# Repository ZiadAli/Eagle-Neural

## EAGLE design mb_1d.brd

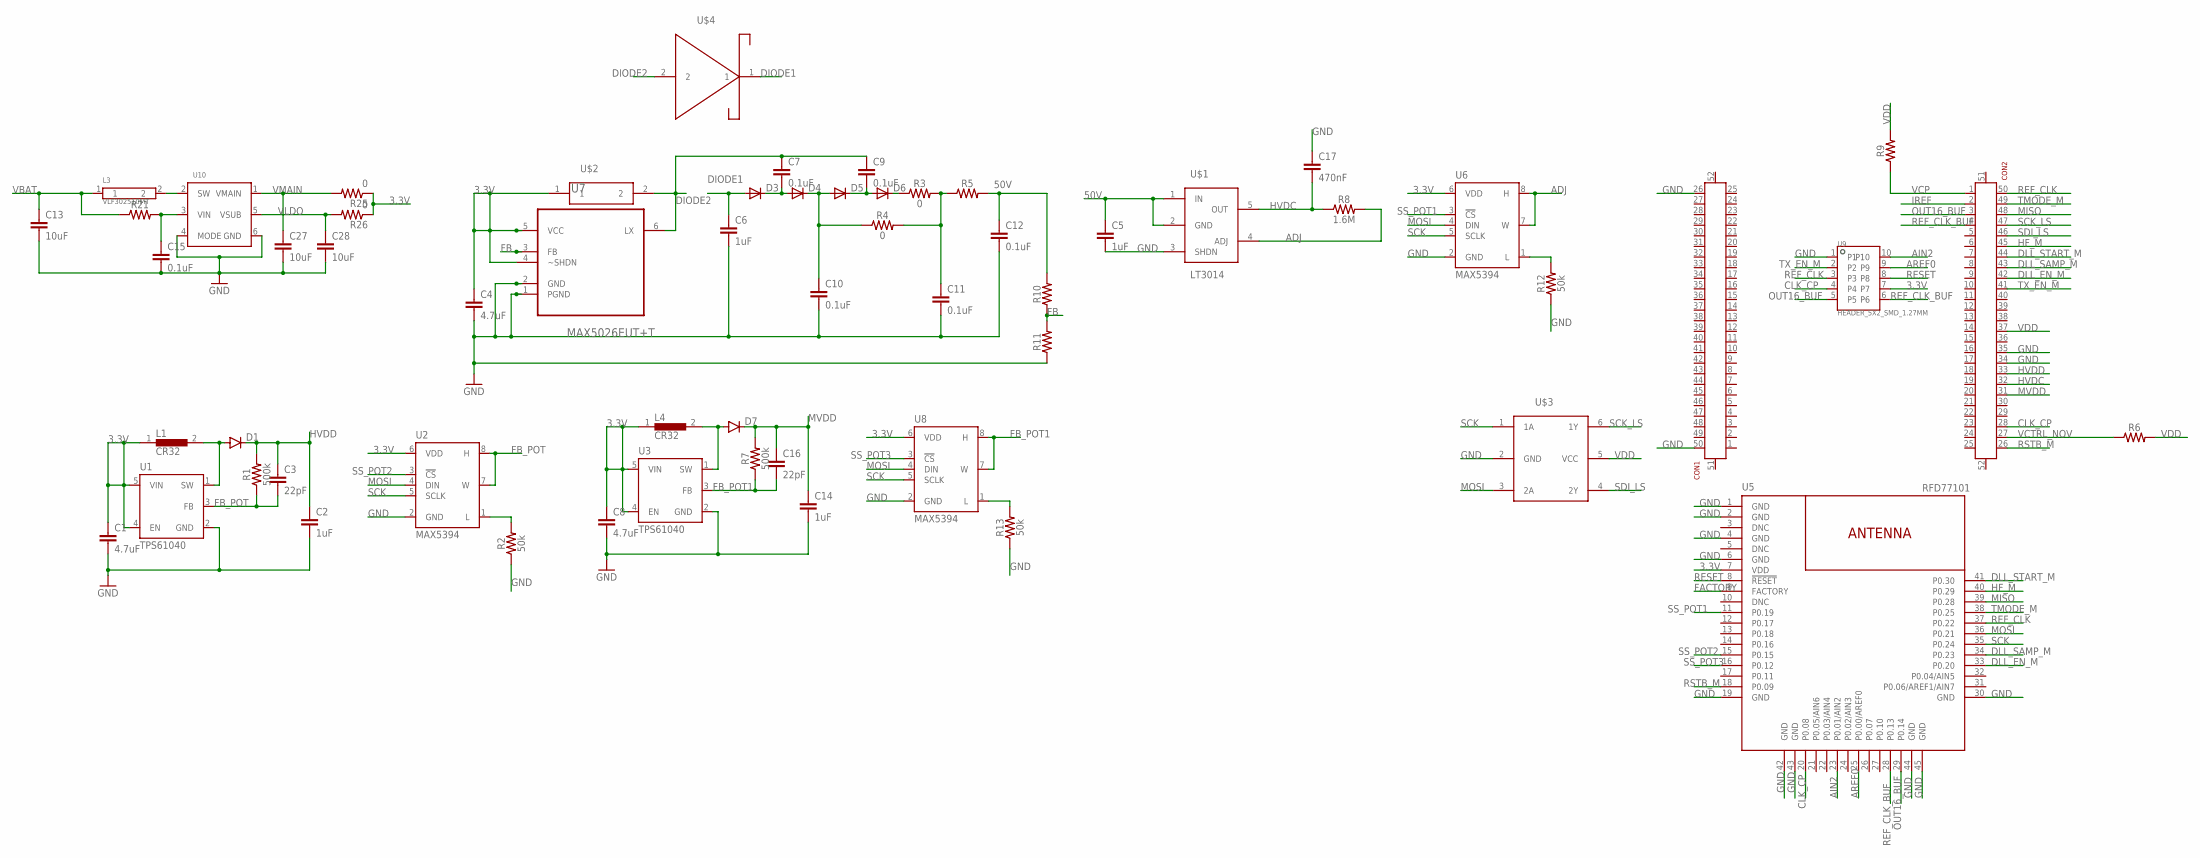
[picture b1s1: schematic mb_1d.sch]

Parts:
C1, C4, C8: 4.7uF; 0805-CAP
C2, C5, C6, C14: 1uF; 1206-CAP
C3, C16: 22pF; 0603-CAP
C7, C9, C10, C11, C12: 0.1uF; 0402
C13, C27, C28: 10uF; 0603-CAP
C15: 0.1uF; 0603-CAP
C17: 470nF; 0402
CON1, CON2: 1013279X_AMPHENOL_2X25; 10132798-052100LF
D1, D7: DIODESOD123; SOD-123
D3, D4, D5, D6: DIODE-SOD323-R; SOD323-R
L1, L4: CR32
L3: VLF302510MT; VLF252010MT
R1, R7: 500k; 0402
R2, R12, R13: 50k; 0402
R3, R4: 0; 0402
R5, R6, R9, R10, R11: 0402
R8: 1.6M; 0402
R21: 0603
R25, R26: 0; 0402-RES
U1, U3: TPS61040; SOT23-5
U2, U6, U8: MAX5394; 8-TDFN-EP
U5: RFD77101
U7: MAX5026EUT+T; SOT95P280X145-6N
U9: HEADER_5X2_SMD_1.27MM
U10: TPS610981; WSON-6
U$1: LT3014
U$2: LQH3NPN470MJRL
U$3: SN74AUP2G34DCKR
U$4: DB2J40700L

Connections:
3.3V: C1.1, C4.1, C8.1, L1.1, L4.1, R25.1, R26.1, U1.4 (EN), U1.5 (VIN), U2.6 (VDD), U3.4 (EN), U3.5 (VIN), U5.7 (VDD), U6.6 (VDD), U7.4 (~SHDN), U7.5 (VCC), U8.6 (VDD), U9.7, U$2.1
50V: C5.1, C12.1, R5.2, R10.2, U$1.1 (IN), U$1.2 (GND)
ADJ: R8.2, U6.7 (W), U6.8 (H), U$1.4 (ADJ)
AIN2: U5.23 (P0.01/AIN2), U9.10
AREF0: U5.25 (P0.00/AREF0), U9.9
CLK_CP: CON2.28, U5.20 (P0.08), U9.4
DIODE1: C6.1, D3.A, U$4.1
DIODE2: C7.1, C9.1, U7.6 (LX), U$2.2, U$4.2
DLL_EN_M: CON2.42, U5.33 (P0.20)
DLL_SAMP_M: CON2.43, U5.34 (P0.23)
DLL_START_M: CON2.44, U5.41 (P0.30)
FACTORY: U5.9 (FACTORY)
FB: R10.1, R11.2, U7.3 (FB)
FB_POT: C3.2, R1.1, U1.3 (FB), U2.7 (W), U2.8 (H)
FB_POT1: C16.2, R7.1, U3.3 (FB), U8.7 (W), U8.8 (H)
GND: C1.2, C2.2, C4.2, C5.2, C6.2, C8.2, C10.2, C11.2, C12.2, C13.2, C14.2, C15.2, C17.1, C27.2, C28.2, CON1.26, CON1.50, CON2.34, CON2.35, R2.1, R11.1, R12.1, R13.1, U1.2 (GND), U2.2 (GND), U3.2 (GND), U5.1 (GND), U5.2 (GND), U5.4 (GND), U5.6 (GND), U5.19 (GND), U5.30 (GND), U5.42 (GND), U5.43 (GND), U5.44 (GND), U5.45 (GND), U6.2 (GND), U7.1 (PGND), U7.2 (GND), U8.2 (GND), U9.1, U10.4 (MODE), U10.6 (GND), U$1.3 (SHDN), U$3.2 (GND)
HF_M: CON2.45, U5.40 (P0.29)
HVDC: C17.2, CON2.32, R8.1, U$1.5 (OUT)
HVDD: C2.1, C3.1, CON2.33, D1.C, R1.2
IREF: CON2.2
MISO: CON2.48, U5.39 (P0.28)
MOSI: U2.4 (DIN), U5.36 (P0.21), U6.4 (DIN), U8.4 (DIN), U$3.3 (2A)
MVDD: C14.1, C16.1, CON2.31, D7.C, R7.2
unnamed: D1.A, L1.2, U1.1 (SW)
unnamed: R2.2, U2.1 (L)
unnamed: C7.2, D3.C, D4.A
unnamed: C10.1, D4.C, D5.A, R4.1
unnamed: C9.2, D5.C, D6.A
unnamed: D6.C, R3.1
unnamed: C11.1, R3.2, R4.2, R5.1
unnamed: D7.A, L4.2, U3.1 (SW)
unnamed: R12.2, U6.1 (L)
unnamed: R13.2, U8.1 (L)
unnamed: L3.2, U10.2 (SW)
unnamed: C15.1, R21.2, U10.3 (VIN)
OUT16_BUF: CON2.3, U5.29 (P0.14), U9.5
REF_CLK: CON2.50, U5.37 (P0.22), U9.3
REF_CLK_BUF: CON2.4, U5.28 (P0.13), U9.6
RESET: U5.8 (!RESET!), U9.8
RSTB_M: CON2.26, U5.18 (P0.09)
SCK: U2.5 (SCLK), U5.35 (P0.24), U6.5 (SCLK), U8.5 (SCLK), U$3.1 (1A)
SCK_LS: CON2.47, U$3.6 (1Y)
SDI_LS: CON2.46, U$3.4 (2Y)
SS_POT1: U5.11 (P0.19), U6.3 (!CS)
SS_POT2: U2.3 (!CS), U5.15 (P0.15)
SS_POT3: U5.16 (P0.12), U8.3 (!CS)
TMODE_M: CON2.49, U5.38 (P0.25)
TX_EN_M: CON2.41, U9.2
VBAT: C13.1, L3.1, R21.1
VCP: CON2.1, R9.1
VCTRL_NOV: CON2.27, R6.1
VDD: CON2.37, R6.2, R9.2, U$3.5 (VCC)
VLDO: C28.1, R26.2, U10.5 (VSUB)
VMAIN: C27.1, R25.2, U10.1 (VMAIN)

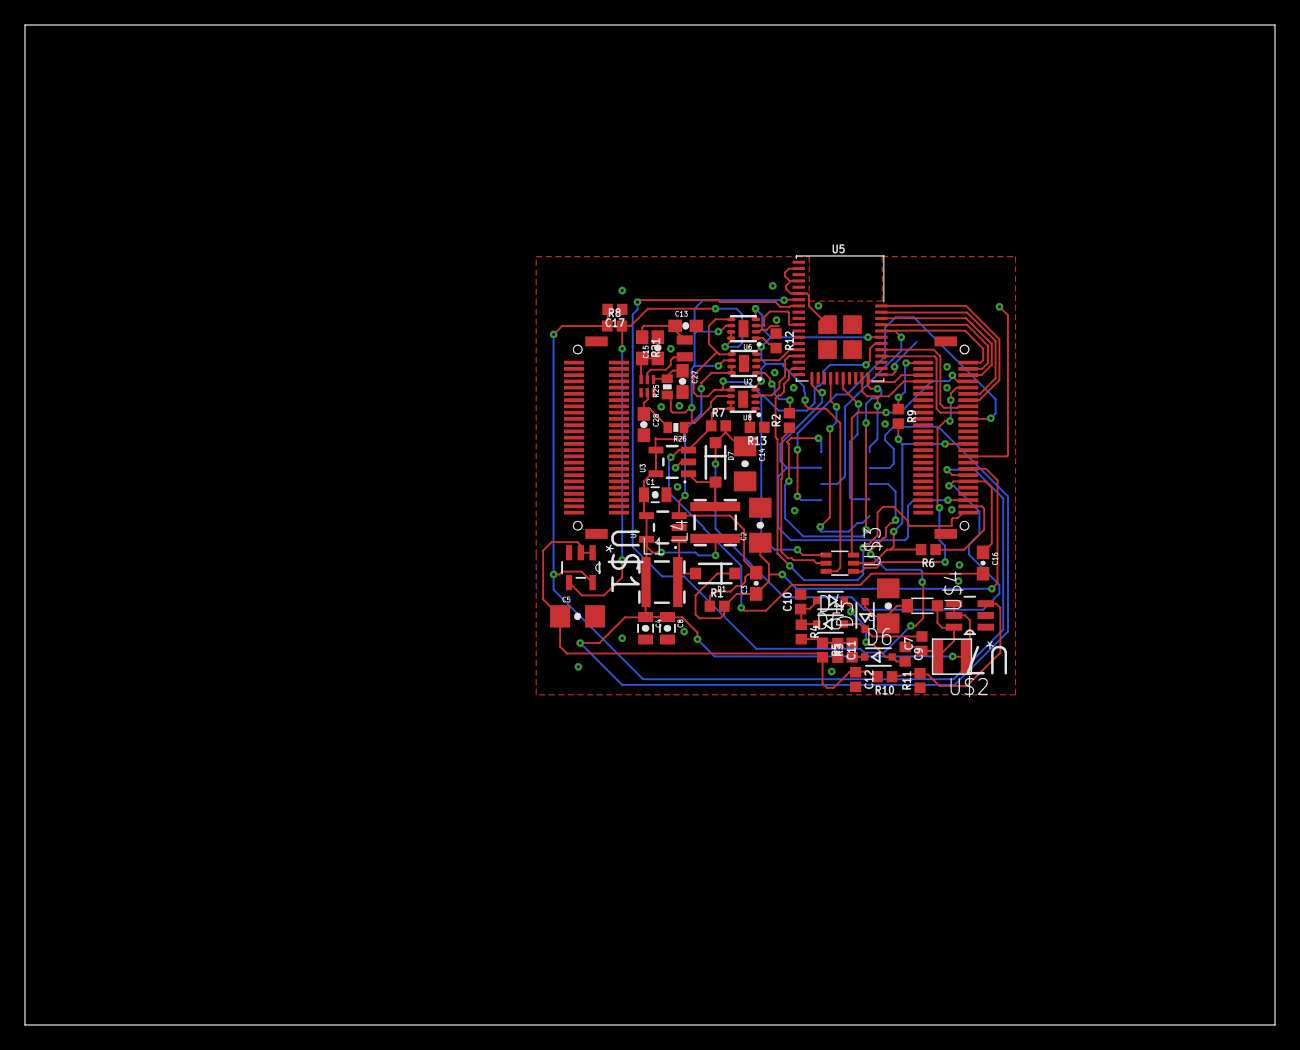
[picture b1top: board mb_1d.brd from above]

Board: 2 copper layers, 100.0 x 80.0 mm, 59 parts (1 on the bottom side), 52 nets.

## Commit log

2017-10-30 First commit to neural
2017-10-30 Began schematic
2017-10-30 Fixed errors
2017-10-31 Added LQH3NPN470MJRL to schematic
2017-11-04 Routed Simblee
2017-11-05 Modified eagle file
2017-11-05 Updated trace properties
2017-11-06 Updated Simblee routes
2017-11-13 First version of completed routing
2017-11-20 Ground pour completed
2017-12-02 Fixed LT3014 error

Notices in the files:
parts and their libraries:
SparkFun-Capacitors: Licensing: Creative Commons ShareAlike 4.0 International - https://creativecommons.org/licenses/by-sa/4.0
SparkFun-RF: © 2015 RF Digital Corporation
